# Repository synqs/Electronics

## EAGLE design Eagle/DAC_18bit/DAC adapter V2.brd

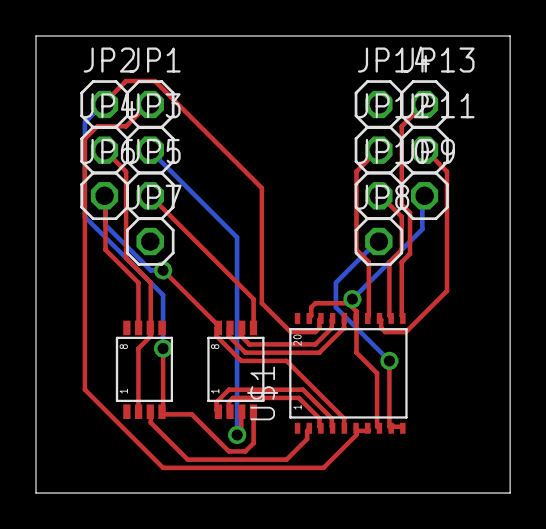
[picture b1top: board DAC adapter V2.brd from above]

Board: 2 copper layers, 26.3 x 25.4 mm, 17 parts (0 on the bottom side), 17 nets.

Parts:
JP1, JP2, JP3, JP4, JP5, JP6, JP7, JP8, JP9, JP10, JP11, JP12, JP13, JP14: 1X01
U$1: AD5781; TSSOP20
U$2: AD8676; MSOP08
U$3: AD8675; MSOP08

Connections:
unnamed: U$1.2, U$3.3
unnamed: JP4.1, U$3.2, U$3.6
unnamed: U$1.16, U$2.7
unnamed: U$1.17, U$2.6
unnamed: U$1.4, U$2.1
unnamed: U$1.3, U$2.2
unnamed: JP1.1, U$1.6, U$1.7
unnamed: JP2.1, U$1.18, U$2.4, U$3.4
unnamed: JP5.1, U$2.5
unnamed: JP3.1, U$2.3
unnamed: JP6.1, U$1.5, U$2.8, U$3.7
unnamed: JP8.1, U$1.9, U$1.10
unnamed: JP9.1, U$1.8, U$1.15, U$1.19
unnamed: JP10.1, U$1.12
unnamed: JP11.1, U$1.13
unnamed: JP12.1, U$1.14
unnamed: JP13.1, U$1.11

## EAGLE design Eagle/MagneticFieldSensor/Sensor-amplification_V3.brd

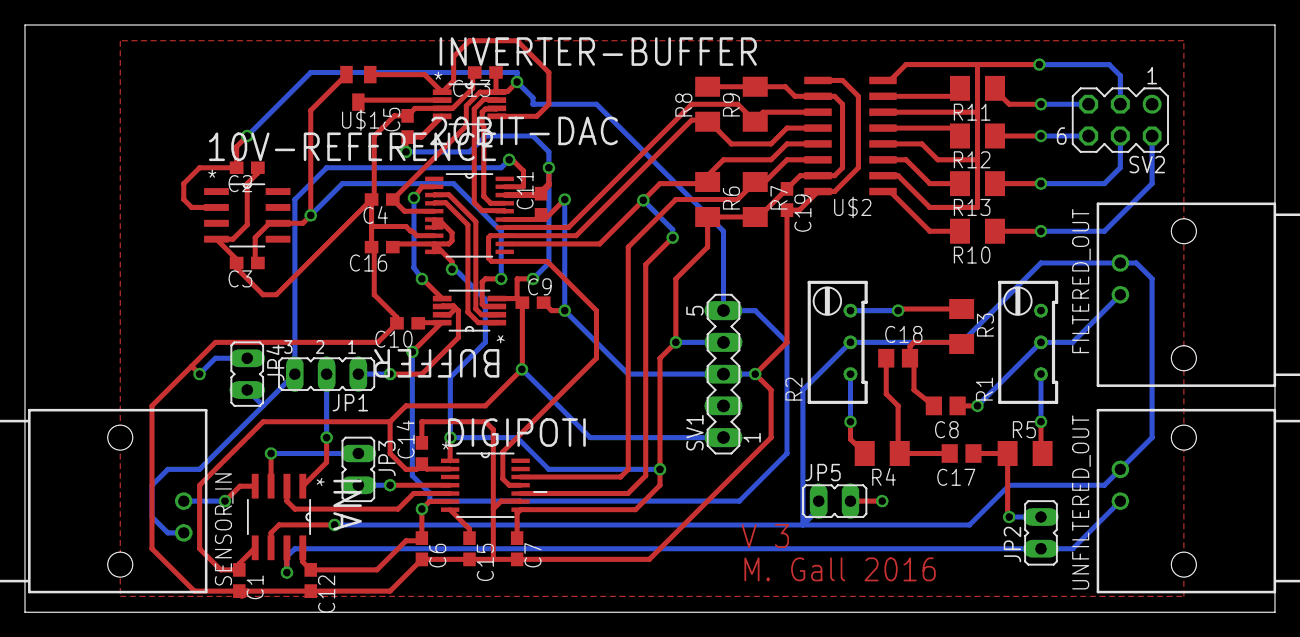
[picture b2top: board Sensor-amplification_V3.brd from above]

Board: 2 copper layers, 100.0 x 47.0 mm, 50 parts (0 on the bottom side), 42 nets.

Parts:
10V-REFERENCE: ADR01BRZ; SOIC127P600X175-8N
20BIT-DAC: AD5791ARUZ; SOP65P640X120-20N
BUFFER: AD8676ARMZ; SOP65P490X110-8N
C1, C2, C3, C4, C5, C6, C7, C9, C10, C11, C12, C13, C14, C16, C19: 100n; C0603
C8, C17, C18: 10n; C0805
C15: 1µ; C0603
DIGIPOTI: AD5293BRUZ-100; SOP65P640X120-14N
FILTERED_OUT: 1-227161-7; AMP_227161
INA: AD8421ARZ; SOIC127P600X175-8N
INVERTER-BUFFER: AD8676ARMZ; SOP65P490X110-8N
JP1: JP2
JP2, JP3, JP4, JP5: JP1
R1: 2k; RTRIM64W
R2: 500; RTRIM64W
R3, R4: 330; M1206
R5: 5600; M1206
R6, R7, R8, R9: 470; M1206
R10, R11, R12, R13: 680; M1206
SENSOR_IN: 1-227161-7; AMP_227161
SV1: MA05-1
SV2: MA03-2
U$1: MPMT2001AT5; SOT23
U$2: ACSL-6400; SO16
UNFILTERED_OUT: 1-227161-7; AMP_227161

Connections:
+5V: 20BIT-DAC.6, 20BIT-DAC.7, 20BIT-DAC.9, 20BIT-DAC.10, C7.1, C16.1, C19.1, DIGIPOTI.1, DIGIPOTI.8, R6.2, R7.2, R8.2, R9.2, SV1.4, U$2.10, U$2.15
+15V: 10V-REFERENCE.2, 20BIT-DAC.5, BUFFER.8, C2.2, C4.1, C6.1, C10.1, C12.1, C13.1, DIGIPOTI.6, INA.8, INVERTER-BUFFER.8, SV1.5
-15V: 20BIT-DAC.18, BUFFER.4, C1.1, C5.1, C9.1, C11.2, C14.1, DIGIPOTI.2, INA.5, INVERTER-BUFFER.4, SV1.1
AGND: 10V-REFERENCE.4, 20BIT-DAC.8, 20BIT-DAC.15, C1.2, C2.1, C3.2, C4.2, C5.2, C6.2, C7.2, C9.2, C10.2, C11.1, C12.2, C13.2, C14.2, C15.2, C16.2, C19.2, DIGIPOTI.9, INVERTER-BUFFER.3, JP4.1, JP5.2, SV1.3, U$2.9, U$2.16
DIN: 20BIT-DAC.12, DIGIPOTI.10, R6.1, U$2.13
unnamed: INA.7, JP2.1, UNFILTERED_OUT.1
unnamed: FILTERED_OUT.2, INA.6, JP5.1, R2.2, UNFILTERED_OUT.2
unnamed: INA.3, JP3.1
unnamed: DIGIPOTI.5, INA.2
unnamed: INA.4, SENSOR_IN.1
unnamed: 20BIT-DAC.19, JP1.3, JP4.2, SENSOR_IN.2
unnamed: INA.1, JP1.2
unnamed: DIGIPOTI.4, JP3.2
unnamed: 10V-REFERENCE.6, BUFFER.3, C3.1, U$1.2
unnamed: 20BIT-DAC.2, BUFFER.5
unnamed: 20BIT-DAC.4, BUFFER.1
unnamed: 20BIT-DAC.3, BUFFER.2
unnamed: INVERTER-BUFFER.2, U$1.3
unnamed: 20BIT-DAC.16, INVERTER-BUFFER.7
unnamed: 20BIT-DAC.17, INVERTER-BUFFER.6
unnamed: INVERTER-BUFFER.1, INVERTER-BUFFER.5, U$1.1
unnamed: C15.1, DIGIPOTI.7
unnamed: C17.2, C18.1, R4.1
unnamed: C8.2, C18.2, R3.2
unnamed: C8.1, FILTERED_OUT.1, R1.2
unnamed: C17.1, JP2.2, R5.1
unnamed: R2.3, R3.1
unnamed: R2.1, R4.2
unnamed: R1.1, R5.2
unnamed: SV2.3, U$2.2, U$2.4, U$2.6, U$2.8
unnamed: R11.2, U$2.7
unnamed: R12.2, U$2.5
unnamed: R13.2, U$2.3
unnamed: R10.1, SV2.2
unnamed: R10.2, U$2.1
unnamed: R13.1, SV2.4
unnamed: R12.1, SV2.6
unnamed: R11.1, SV2.5
SCLK: 20BIT-DAC.13, DIGIPOTI.11, R8.1, U$2.12
SUBSTRACT_SELECT: BUFFER.6, BUFFER.7, JP1.1
SYNC-DAC: 20BIT-DAC.14, R9.1, U$2.11
SYNC-POTI: DIGIPOTI.12, R7.1, U$2.14

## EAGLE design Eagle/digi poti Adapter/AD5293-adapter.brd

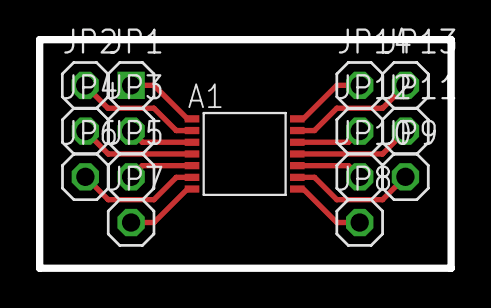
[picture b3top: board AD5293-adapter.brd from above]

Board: 2 copper layers, 22.9 x 12.7 mm, 15 parts (0 on the bottom side), 14 nets.

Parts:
A1: AD5293
JP1: 1X01-SQUARE
JP2, JP3, JP4, JP5, JP6, JP7, JP8, JP9, JP10, JP11, JP12, JP13, JP14: 1X01

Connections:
unnamed: A1.1, JP1.1
unnamed: A1.2, JP2.1
unnamed: A1.3, JP3.1
unnamed: A1.4, JP4.1
unnamed: A1.5, JP5.1
unnamed: A1.7, JP7.1
unnamed: A1.8, JP8.1
unnamed: A1.9, JP9.1
unnamed: A1.10, JP10.1
unnamed: A1.11, JP11.1
unnamed: A1.12, JP12.1
unnamed: A1.13, JP13.1
unnamed: A1.14, JP14.1
unnamed: A1.6, JP6.1

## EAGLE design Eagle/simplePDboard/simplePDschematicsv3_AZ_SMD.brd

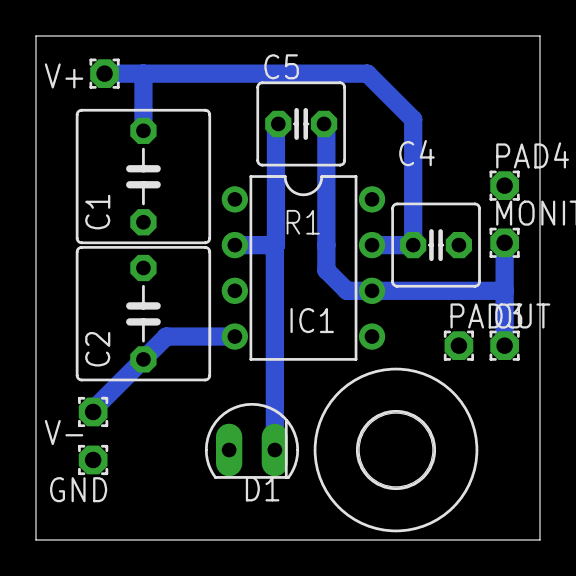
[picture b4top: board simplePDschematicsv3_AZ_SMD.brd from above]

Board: 1 copper layer, 28.0 x 28.0 mm, 15 parts (1 on the bottom side), 5 nets.

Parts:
C1, C2: 47uF; C050-075X075
C4: 1nF; C025-050X050
C5: 100pF; C025-050X050
D1: SFH206
GND: 1,6/0,9
H1: 4.1; 4,1
IC1: TL071P; DIL08
MONITOR: 1,6/0,9
OUT: 1,6/0,9
PAD3, PAD4: 1,6/0,9
R1: 10k; M1206
V+: 1,6/0,9
V-: 1,6/0,9

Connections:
GND: C1.1, C2.2, C4.2, D1.A, GND.1, IC1.3, PAD3.1, PAD4.1
unnamed: C5.2, IC1.6, MONITOR.1, OUT.1, R1.2
unnamed: C5.1, D1.K, IC1.2, R1.1
V+: C1.2, C4.1, IC1.7, V+.1
V-: C2.1, IC1.4, V-.1

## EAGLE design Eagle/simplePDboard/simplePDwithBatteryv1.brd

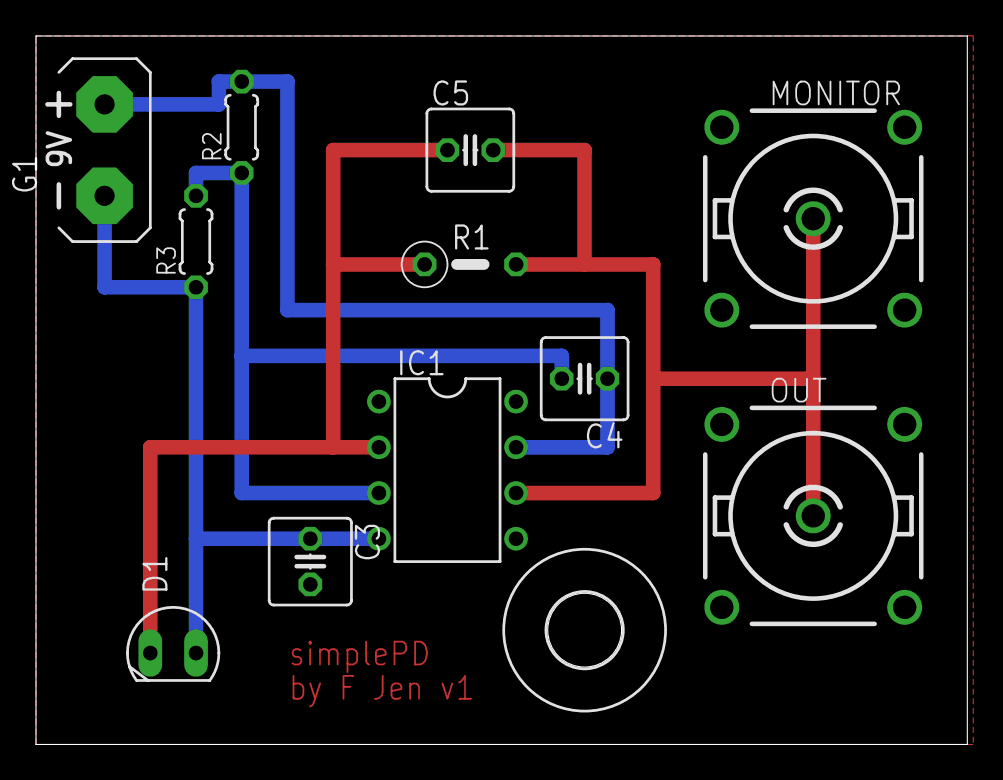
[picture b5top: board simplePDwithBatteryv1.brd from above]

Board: 2 copper layers, 51.7 x 39.4 mm, 12 parts (0 on the bottom side), 5 nets.

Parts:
C3, C4: 1nF; C025-050X050
C5: 4,7pF; C025-050X050
D1: SFH205
G1: AB9V
H1: MOUNT-HOLE4.1; 4,1
IC1: OP27Z; DIL08
MONITOR: R141426
OUT: R141426
R1: 10k; 0207/5V
R2, R3: 10k; 0204/5

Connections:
GND: C3.2, C4.2, IC1.3, MONITOR.2, MONITOR.3, MONITOR.4, MONITOR.5, OUT.2, OUT.3, OUT.4, OUT.5, R2.1, R3.2
unnamed: C5.1, D1.K, IC1.2, R1.1
unnamed: C5.2, IC1.6, MONITOR.1, OUT.1, R1.2
V+: C4.1, G1.+, IC1.7, R2.2
V-: C3.1, D1.A, G1.-, IC1.4, R3.1
